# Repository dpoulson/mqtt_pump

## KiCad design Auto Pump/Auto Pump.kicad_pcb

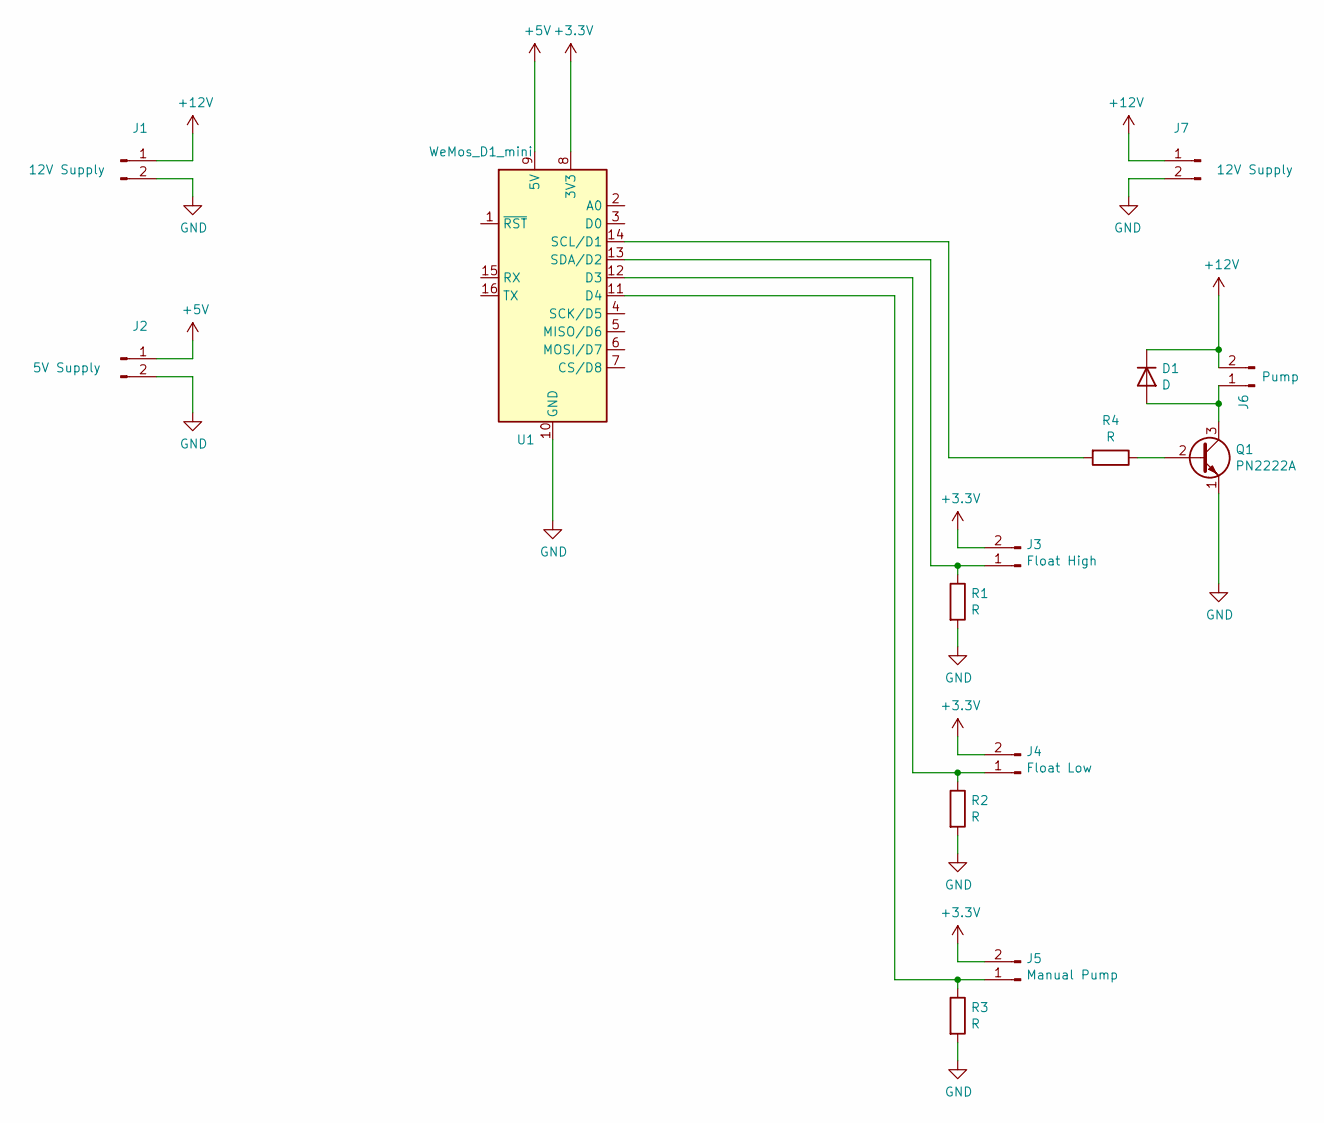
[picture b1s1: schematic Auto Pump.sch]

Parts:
D1: D; D_A-405_P12.70mm_Horizontal
J1, J7: 12V Supply; PinHeader_1x02_P2.54mm_Vertical
J2: 5V Supply; PinHeader_1x02_P2.54mm_Vertical
J3: Float High; PinHeader_1x02_P2.54mm_Vertical
J4: Float Low; PinHeader_1x02_P2.54mm_Vertical
J5: Manual Pump; PinHeader_1x02_P2.54mm_Vertical
J6: Pump; PinHeader_1x02_P2.54mm_Vertical
Q1: PN2222A; TO-92_Inline
R1, R2, R3, R4: R; R_Axial_DIN0309_L9.0mm_D3.2mm_P12.70mm_Horizontal
U1: WeMos_D1_mini; WEMOS_D1_mini_light

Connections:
+3V3: J3.2, J4.2, J5.2, U1.8 (3V3)
+5V: J2.1, U1.9 (5V)
+12V: D1.1 (K), J1.1, J6.2, J7.1
GND: J1.2, J2.2, J7.2, Q1.1 (E), R1.2, R2.2, R3.2, U1.10 (GND)
unnamed: D1.2 (A), J6.1, Q1.3 (C)
unnamed: J3.1, R1.1, U1.13 (SDA/D2)
unnamed: J4.1, R2.1, U1.12 (D3)
unnamed: J5.1, R3.1, U1.11 (D4)
unnamed: Q1.2 (B), R4.1
unnamed: R4.2, U1.14 (SCL/D1)

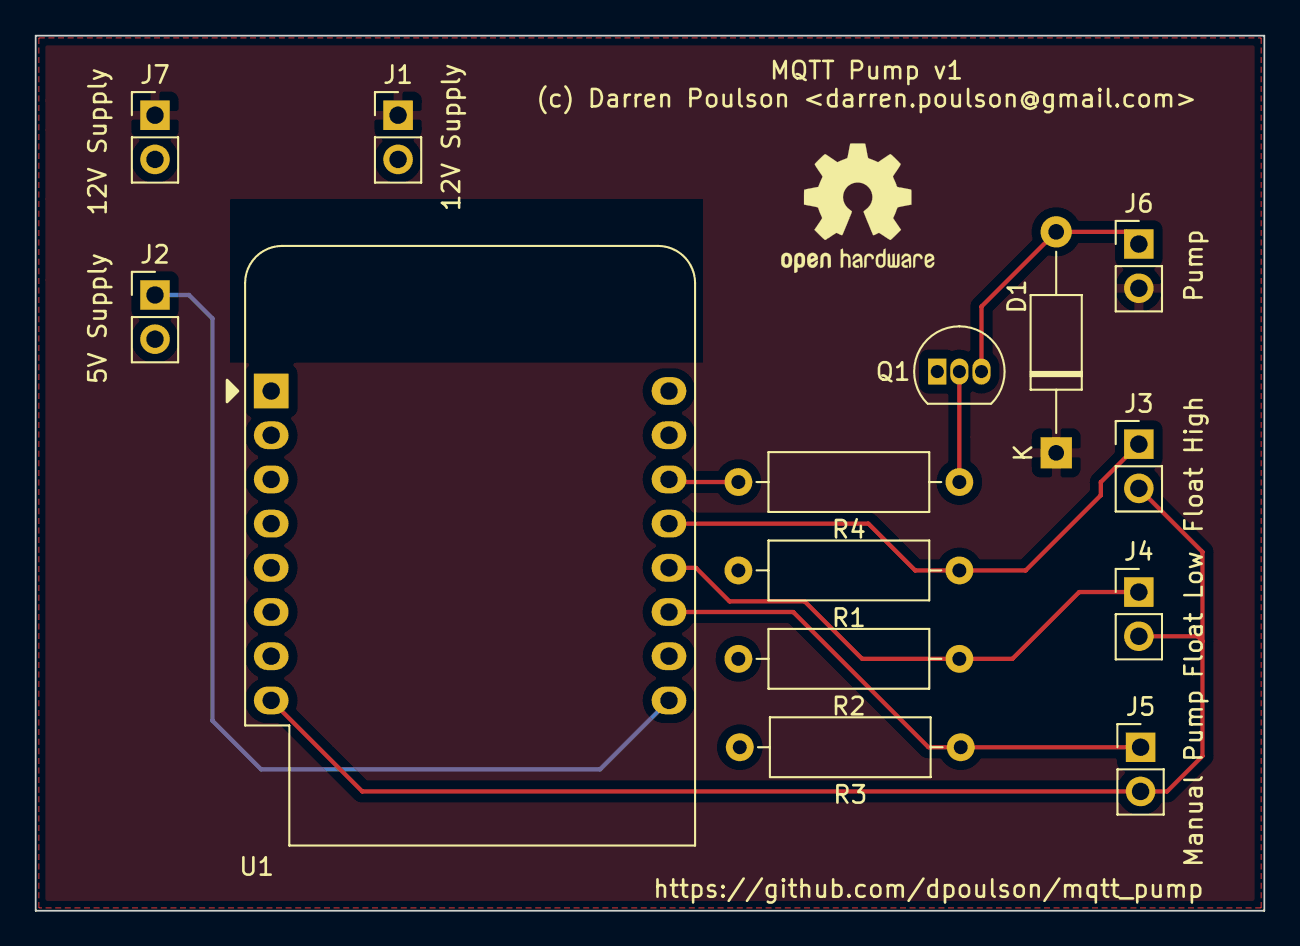
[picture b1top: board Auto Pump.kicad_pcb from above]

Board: 2 copper layers, 70.6 x 50.3 mm, 14 parts (0 on the bottom side), 10 nets.

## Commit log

2021-05-11 KiCAD Files
2021-05-11 Added gitignore and start of arduino code
2021-05-19 First pass at arduino code using Homie standard
